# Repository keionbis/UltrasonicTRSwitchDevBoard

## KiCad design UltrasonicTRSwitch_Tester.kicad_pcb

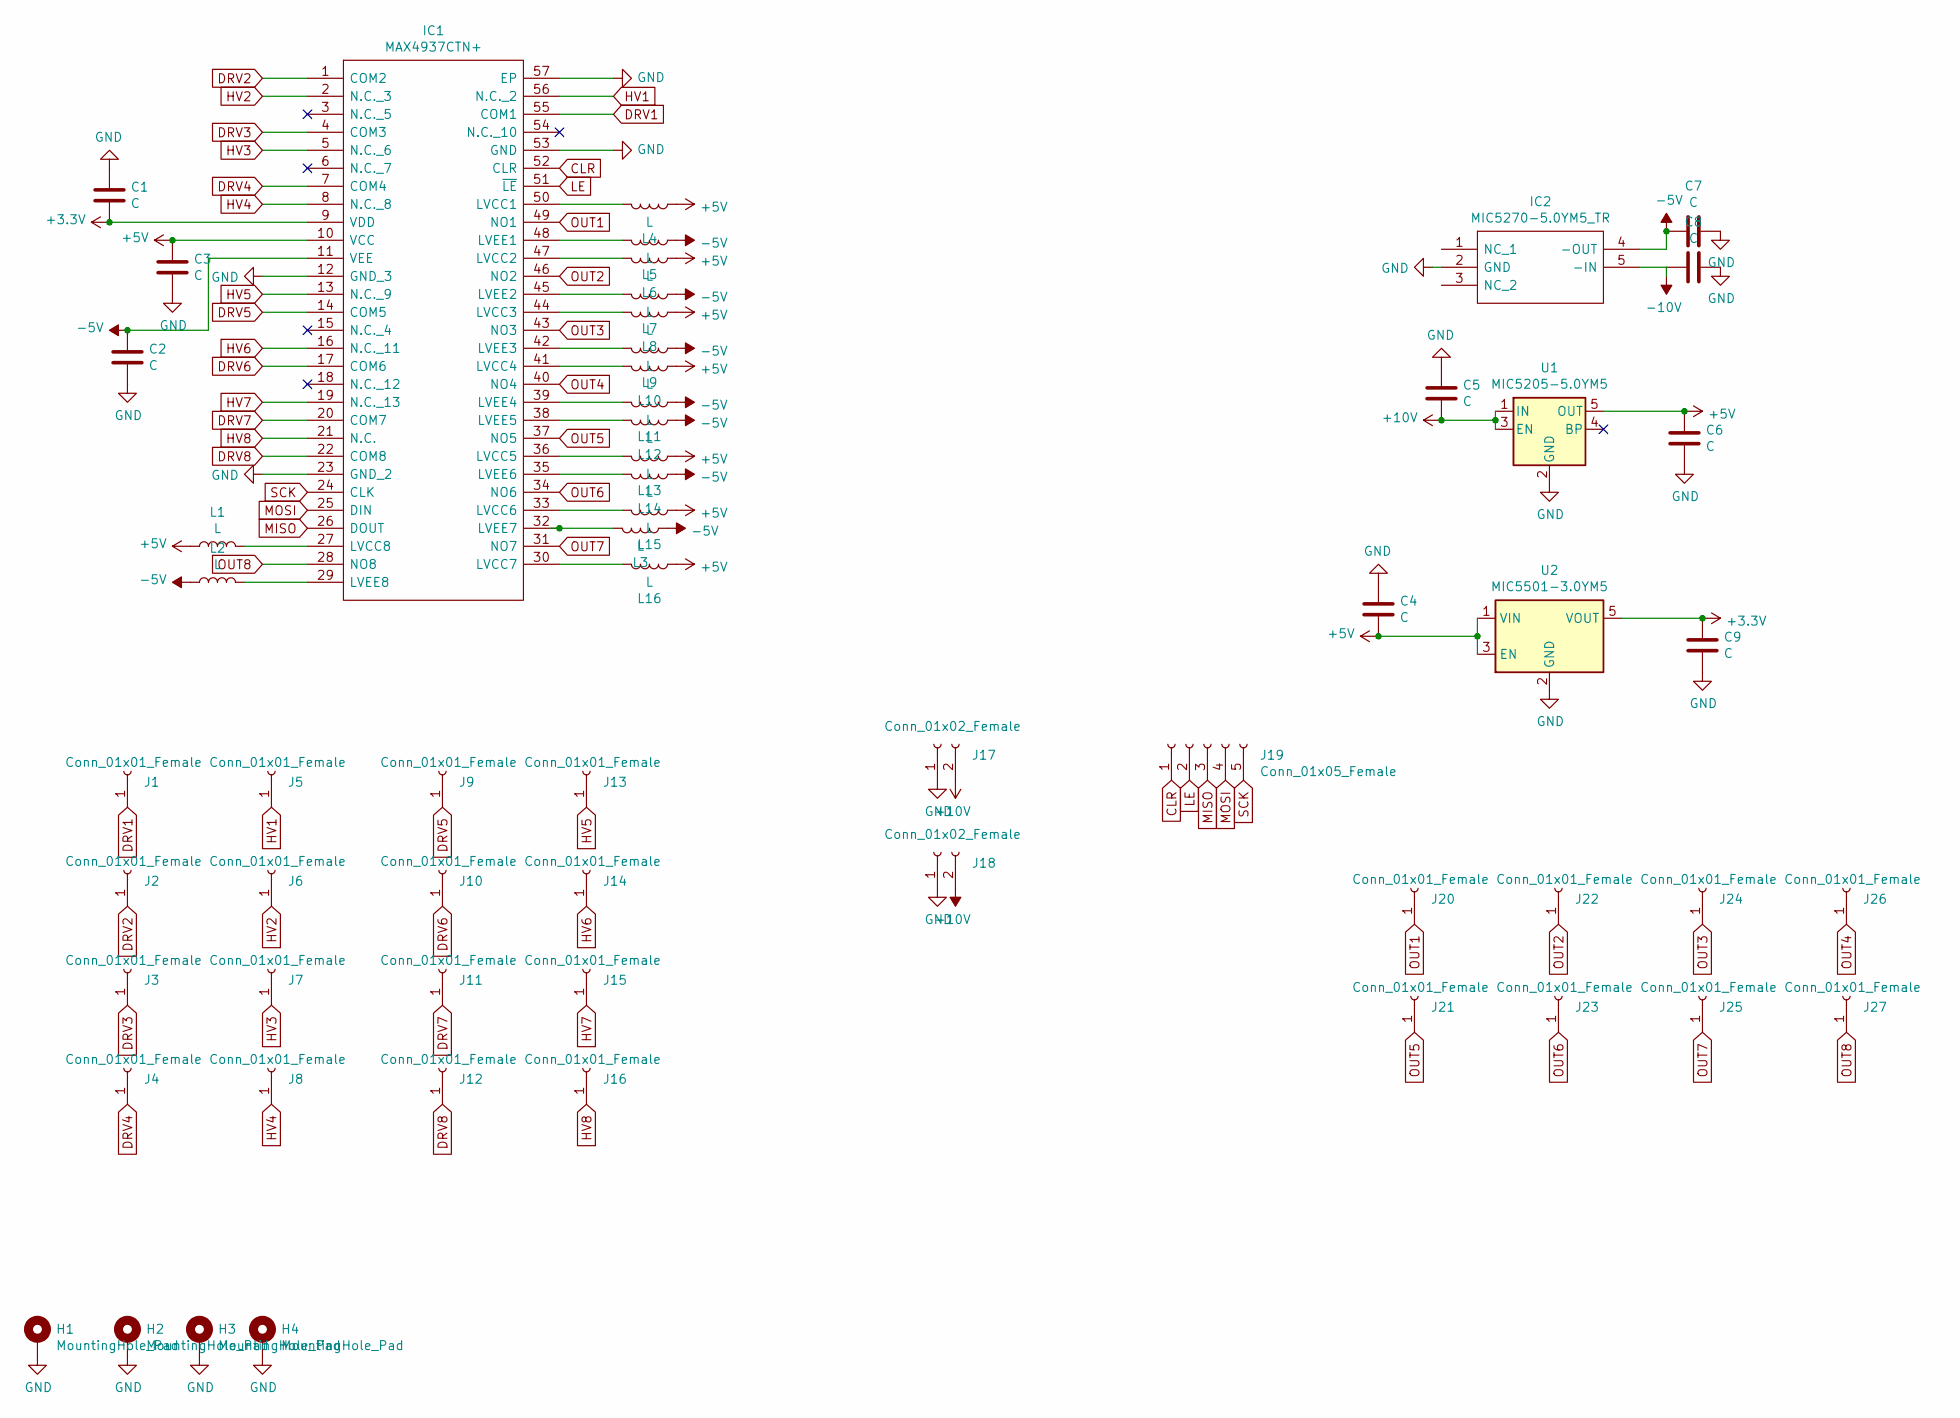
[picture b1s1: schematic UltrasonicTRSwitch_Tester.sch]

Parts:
C1, C2, C3, C4, C5, C6, C7, C8, C9: C; C_0603_1608Metric
H1, H2, H3, H4: MountingHole_Pad; MountingHole_3.2mm_M3_ISO7380_Pad
IC1: MAX4937CTN+; QFN50PX500X1100X80-57N; Manufacturer_Part_Number MAX4937CTN+; Mouser Part Number 700-MAX4937CTN+
IC2: MIC5270-5.0YM5_TR; SOT95P280X145-5N; Manufacturer_Part_Number MIC5270-5.0YM5 TR
J1, J2, J3, J4, J5, J6, J7, J8, J9, J10, J11, J12, J13, J14, J15, J16: Conn_01x01_Female; TestPoint_Pad_4.0x4.0mm
J17, J18: Conn_01x02_Female; Banana_Jack_2Pin
J19: Conn_01x05_Female; PinHeader_1x05_P2.54mm_Vertical
J20, J21, J22, J23, J24, J25, J26, J27: Conn_01x01_Female; TestPoint_Pad_2.5x2.5mm
L1, L2, L3, L4, L5, L6, L7, L8, L9, L10, L11, L12, L13, L14, L15, L16: L; L_0603_1608Metric
U1: MIC5205-5.0YM5; SOT-23-5
U2: MIC5501-3.0YM5; SOT-23-5

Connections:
+3V3: C1.2, C9.1, IC1.9 (VDD), U2.5 (VOUT)
+5V: C3.1, C4.2, C6.1, IC1.10 (VCC), L1.1, L4.1, L6.1, L8.1, L10.1, L13.1, L15.1, L16.1, U1.5 (OUT), U2.1 (VIN), U2.3 (EN)
+10V: C5.2, J17.2, U1.1 (IN), U1.3 (EN)
-5V: C2.1, C7.2, IC1.11 (VEE), IC2.4 (-OUT), L2.1, L3.1, L5.1, L7.1, L9.1, L11.1, L12.1, L14.1
-10V: C8.2, IC2.5 (-IN), J18.2
CLR: IC1.52 (CLR), J19.1
DRV1: IC1.55 (COM1), J1.1
DRV2: IC1.1 (COM2), J2.1
DRV3: IC1.4 (COM3), J3.1
DRV4: IC1.7 (COM4), J4.1
DRV5: IC1.14 (COM5), J9.1
DRV6: IC1.17 (COM6), J10.1
DRV7: IC1.20 (COM7), J11.1
DRV8: IC1.22 (COM8), J12.1
GND: C1.1, C2.2, C3.2, C4.1, C5.1, C6.2, C7.1, C8.1, C9.2, H1.1, H2.1, H3.1, H4.1, IC1.12 (GND_3), IC1.23 (GND_2), IC1.53 (GND), IC1.57 (EP), IC2.2 (GND), J17.1, J18.1, U1.2 (GND), U2.2 (GND)
HV1: IC1.56 (N.C._2), J5.1
HV2: IC1.2 (N.C._3), J6.1
HV3: IC1.5 (N.C._6), J7.1
HV4: IC1.8 (N.C._8), J8.1
HV5: IC1.13 (N.C._9), J13.1
HV6: IC1.16 (N.C._11), J14.1
HV7: IC1.19 (N.C._13), J15.1
HV8: IC1.21 (N.C.), J16.1
LE: IC1.51 (~LE), J19.2
MISO: IC1.26 (DOUT), J19.3
MOSI: IC1.25 (DIN), J19.4
unnamed: IC1.27 (LVCC8), L1.2
unnamed: IC1.29 (LVEE8), L2.2
unnamed: IC1.30 (LVCC7), L16.2
unnamed: IC1.32 (LVEE7), L3.2
unnamed: IC1.33 (LVCC6), L15.2
unnamed: IC1.35 (LVEE6), L14.2
unnamed: IC1.36 (LVCC5), L13.2
unnamed: IC1.38 (LVEE5), L12.2
unnamed: IC1.39 (LVEE4), L11.2
unnamed: IC1.41 (LVCC4), L10.2
unnamed: IC1.42 (LVEE3), L9.2
unnamed: IC1.44 (LVCC3), L8.2
unnamed: IC1.45 (LVEE2), L7.2
unnamed: IC1.47 (LVCC2), L6.2
unnamed: IC1.48 (LVEE1), L5.2
unnamed: IC1.50 (LVCC1), L4.2
OUT1: IC1.49 (NO1), J20.1
OUT2: IC1.46 (NO2), J22.1
OUT3: IC1.43 (NO3), J24.1
OUT4: IC1.40 (NO4), J26.1
OUT5: IC1.37 (NO5), J21.1
OUT6: IC1.34 (NO6), J23.1
OUT7: IC1.31 (NO7), J25.1
OUT8: IC1.28 (NO8), J27.1
SCK: IC1.24 (CLK), J19.5

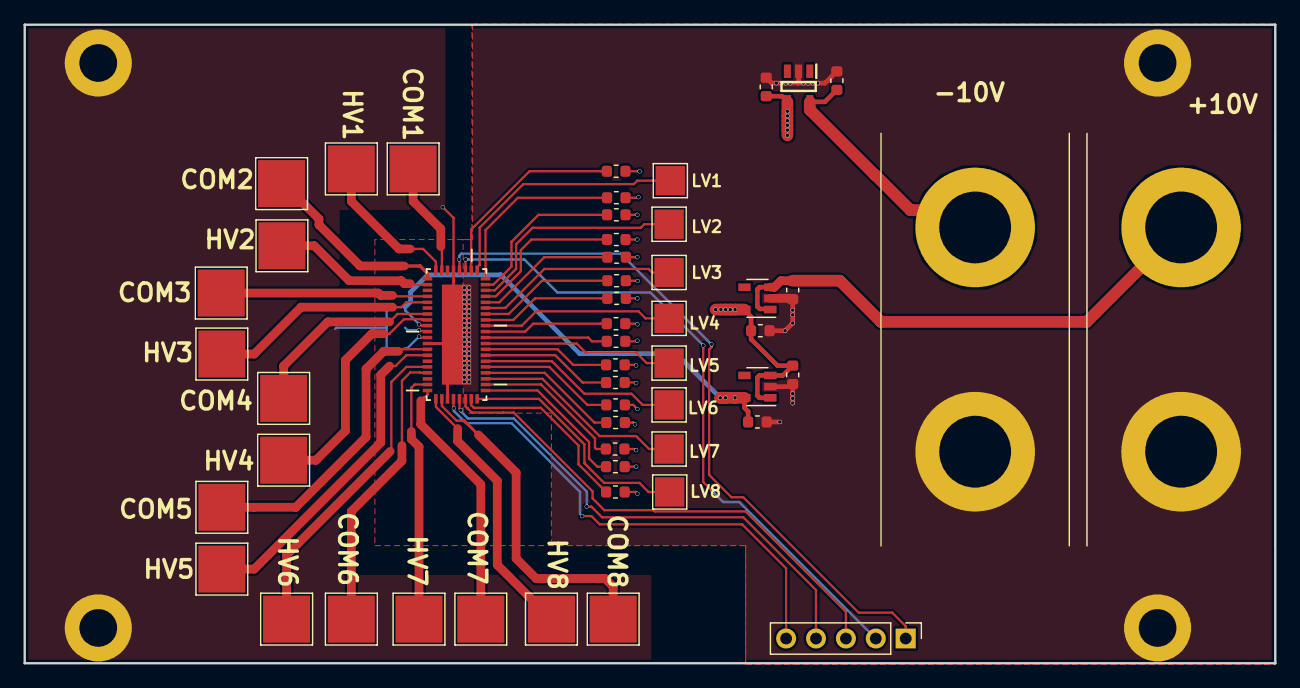
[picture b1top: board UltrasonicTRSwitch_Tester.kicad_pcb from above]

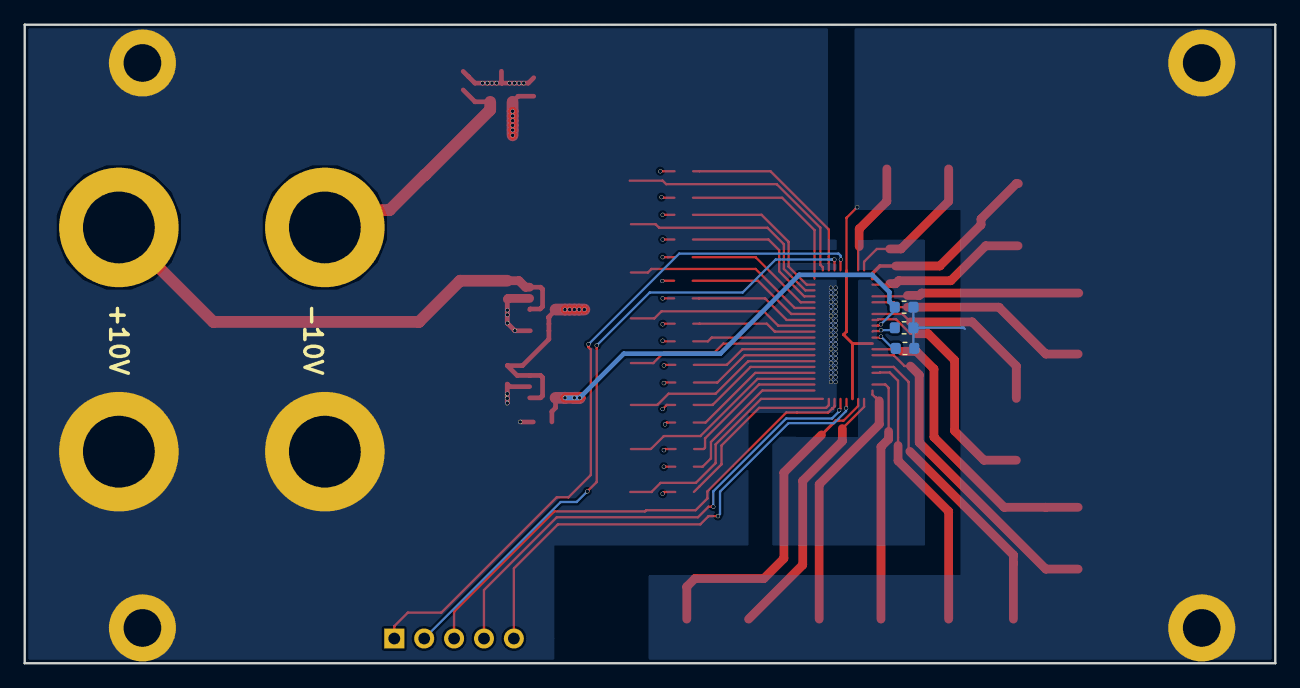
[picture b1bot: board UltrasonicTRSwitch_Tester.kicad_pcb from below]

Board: 4 copper layers, 106.2 x 54.2 mm, 60 parts (3 on the bottom side), 51 nets.

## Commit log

2019-02-18 Initial Commit, First rev
2019-02-18 Updated footprints and board size
